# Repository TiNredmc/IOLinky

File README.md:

# IOLinky

IOLinky is an attempt to implement an open-source bare-minimum working IO-Link device.
This project is the part of the undergraduate Automation engineering Co-operative education project while working as R&D internship at Delta Electrnics (Thailand) PCL. From King Mongkut's Institute of Technology Ladkrabang (KMITL). 

**WARNING: THIS SOFTWARE IS NOT MEANT TO BE USED IN COMMERCIAL PRODUCT, I, THIPOK JIAMJARAPAN WILL NOT BE RESPONSIBLE FOR ANY FAILURES/MULFUNCTIONS CAUSED BY THE USE OF THIS SOFTWARE (OR ANY MATERIAL OF THIS PROJECT) IN THE COMMERCIAL PRODUCT, ESPECIALLY SAFETY-RELATED PRODUCT. USER WHO INSISTED TO USE THIS SOFTWARE IN COMMERCIAL PRODUCT WILL HAVE TO TAKE ALL THE RISK ON YOUR OWN. GOOD LUCK, YOU HAVE BE WARNED**

The example application of the IOLinky is the 24 to 5 VDC buck converter, with the feature of input and output monitoring plus Efuse (I2t) implementation.

The original goal of IOLinky is to build the bare-minimum IO-Link compatible device. But the software stack is endded up working quite well. This will soon shifted from a single-use code to the library-code approach. Contribution to project are appreciately welcome!

# Acknowledgement 

This project was made possible by the generous support from these great individuals.
 - **Mr. P. Haribabu**, RD Firmware engineer from **Delta Electronics (Thailand) PCL** for the internship opportunity and project supervision. 
 - **Mr. Steve Liang**, Technical engineer from **STMicroelectronics** for the IO-Link technical support. 
 - **Wurth Electronics (Thailand) Co., Ltd** for providing free component samples to be used in this project.  
 - **Assoc.Prof.Dr. Apinai Rerkratn** from Automation engineering department, school of engineering **KMITL**.

# General Info

- COM modes
    - Peak COM3 response time (L6362A + STM32F042) at **```51.2us```** 
	- Peak COM3 response time (L6362A + GD32E230F8 + New UART API) at **```33.0us```**
    - Cycle time is **```20.00ms```**
    - Supported all COM modes. But may have spec unmet
    - COM3 **SPEC MET✔️**  (IOLinky v1.0 only, for now)
    - COM2 **SPEC MET✔️**
    - COM1 **SPEC MET✔️**

- M-sequence types (Code-customizable)
    - ```M_TYPE_0``` in **Startup** and **Pre-operate** mode
    - ```M_TYPE_2_2``` or ```M_TYPE_2_V``` in **Operate** mode

- Page (Direct parameters)
    - Direct parameter 1 with master command for switching between operation mode
    - Read / Write the Direct parameter 2 is supported

- ISDU 
    - Read / Write system command (unused for now)
    - Basic mandatory info such as Product ID and Vendor ID
    - Process Data Input only (M_TYPE_2_2 and M_TYPE_2_V)

- Process Data
    - 16 Bit PD input with ```M_TYPE_2_2```
    - 8 octet PD input with ```M_TYPE_2_V``` (IOLinky v1.0)
    - PD output is not implemented at this time of writing but possible

# TODO
- Code separation as a standalone library

- M-sequence
    - Check Master's CKT

- ISDU
    - Vendor command for fun
    - Data storage feature
    
- Event
    - Implement event/diagnostic feature

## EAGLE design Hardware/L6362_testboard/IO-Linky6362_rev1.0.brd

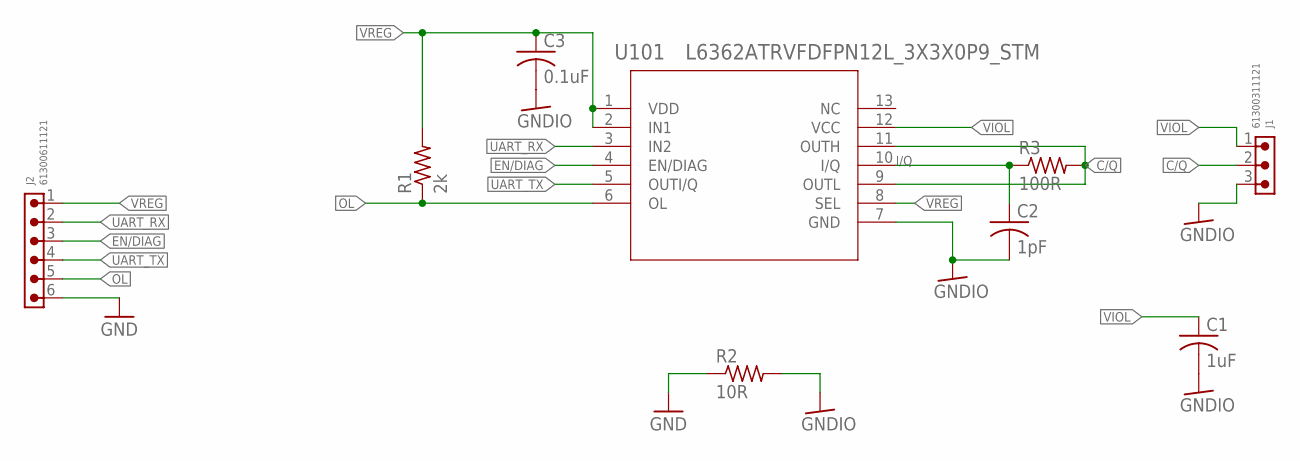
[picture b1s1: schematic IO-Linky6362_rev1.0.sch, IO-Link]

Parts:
C1: 1uF; C0603K
C2: 1pF; C0603K
C3: 0.1uF; C0603K
J1: 61300311121
J2: 61300611121
R1: 2k; R0603
R2: 10R; R0603
R3: 100R; R0603
U101: L6362ATRVFDFPN12L_3X3X0P9_STM; VFDFPN12L_3X3X0P9_STM

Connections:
C/Q: J1.2, R3.2, U101.9 (OUTL), U101.11 (OUTH)
EN/DIAG: J2.3, U101.4 (EN/DIAG)
GND: J2.6, R2.1
GNDIO: C1.2, C2.2, C3.2, J1.3, R2.2, U101.7 (GND)
I/Q: C2.1, R3.1, U101.10 (I/Q)
OL: J2.5, R1.1, U101.6 (OL)
UART_RX: J2.2, U101.3 (IN2)
UART_TX: J2.4, U101.5 (OUTI/Q)
VIOL: C1.1, J1.1, U101.12 (VCC)
VREG: C3.1, J2.1, R1.2, U101.1 (VDD), U101.2 (IN1), U101.8 (SEL)

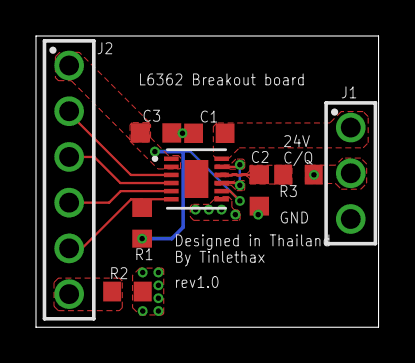
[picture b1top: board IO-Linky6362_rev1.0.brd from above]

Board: 2 copper layers, 19.0 x 16.2 mm, 9 parts (0 on the bottom side), 10 nets.

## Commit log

2024-07-10 Initial
2024-07-10 Updated SPI FSM
2024-07-10 Added dummy hardfault handler.
2024-07-10 Changed Blinking LED to LED2 (Green) and shorten the breathing pattern.
2024-07-10 Change Optimization level back to -Obalance
2024-07-11 Properly check the RXNE flag.
2024-07-18 Place holder for IO-Link System manager.
2024-07-18 Introduced fast FIFO read and write.
2024-07-18 Now using COM2 and changed the polling method.
2024-07-18 Place holder for IO-Link Application layer.
2024-07-18 Added GPIO for monitoring IO-Link activity (for oscilliscope triggering).
2024-07-18 Can reply to Direct parameter 1 and enter PREOPERATE and OPERATE mode. TODO : Reply ISDU in OPREATE MODE.
2024-07-18 Now utilizing Red and Green to show IO-Link connection status. TODO : detect disconnect.
2024-07-18 Moved iol_sm.h to src_iol folder.
2024-07-18 OPERATE mode is now working (NOT FULLY YET). TODO : Complete the ISDU R/W system in DL.
2024-07-18 Updated README.
2024-07-18 Updated Keil project file just to keep it complete.
2024-07-23 Big updates. - Device parameter page 1 data moved to the upper layer (to the Application layer). - Added communication timeout, fall back to STARTUP mode after certain period of time if no comm. - Ad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
2024-07-23 basic ISDU is almost working. TODO : rewrite the PD read.
2024-07-24 Process Data is now working. Added more code comments.
2024-07-24 keep these latest.
2024-07-24 Added checks for L6364 hw fault
    Added a timeout for R/W operations with L6364 cause infinite loops scares af
2024-07-25 Typo fix and minor bugfix
    Fixed some syntax error and a minor bug.
    Calling spi_l6364FastWriteFF with count > 0x0F would have resulted in return 0 (aka 0 bytes remaining to transmit)
2024-07-25 Moved #include "Systick_delay.h" from spi.c to spi.h
    Following mantainer coding standard
2024-07-26 Process Data will only update when necessary to prevent weird bug. IO-Link timeout reset depends on ISDU Flow control Idle command.
2024-07-30 Solved the periodically missing PD data. Added process data write for later use.
2024-07-30 Update PD every 100ms.
2024-07-30 Update to keep track.
2024-07-30 Added schematic and board file for L6362 breakout board(Experiment).
2024-08-01 Added shadow memory for the Process Data.
2024-08-01 Added more ISDU read capabilities.
2024-08-01 Added IODD example file.
2024-08-01 Corrected the ISDU index's endianess.
2024-08-01 Added ISDU write handling (Untested) and currected the memcpy length of ISDU product name.
2024-08-01 added gitignore.
2024-08-01 Moved some part of ISDU data upto the Application layer.
2024-08-01 Changed Process Data display and added unit code.
2024-08-01 Another attempt to fix periodically missing PD, also removed PD write and read funciton (temporary).
2024-08-06 Added code for IOLink-F042. Using L6362 instead of L6364.
2024-08-06 Added L6362A datasheet
2024-08-06 corrected CKS checksum calculation and stripped down the main_fsm.
2024-08-08 Improved response speed, need to test with real L6362A.
2024-08-14 Added missing break in iol_dl_craftISDUWrite().
2024-08-14 removed one line for unknown reason.
2024-08-14 Implemented the Direct parameter 2 and updated Product name.
2024-08-14 EN pin of L6362A will be a forced output instead of Pull-up OD.
2024-08-14 Fixed the missing uart bit and TX switching too early issue.
2024-08-14 Update to keep it in touch.
2024-08-14 Added General Info and TODO.
2024-08-19 function names are now startin with usart. Also preparing for USART DMA TX.
2024-08-19 Added ADC driver.
2024-08-19 PD is not the read value from ADC.
2024-08-19 updated pin out.
2024-08-19 updated function name according to update to usart driver.
2024-08-19 extended timout a bit and also always check mtype before decode the message.
2024-08-19 Update ADC read demo every 20ms.
2024-08-19 Updated IODD bitrate description to COM2.
2024-08-19 Fixed the I-service of ISDU write and also calculated checksum for the reply.
2024-08-27 Added PDF files of first prototype hardware
2024-08-27 Documents for GD32E230F8 that will be used in the first prototype.
2024-08-27 Added code for IOLinky v1.0 (GD32E230 based).
2024-08-28 Added oen highlight to some important details in the datasheet.
2024-08-28 Keep track of the project file.
2024-08-28 TODO : check the time out.
2024-08-28 corrected baud rate on 72MHz APB clock.
2024-08-28 separated IO-Link Data Link layer parts into different files.
2024-08-28 Currently using HXTAL, will revert back to IRC8M soon. As the first prototype doesn't have XTAL.
2024-08-28 Corrected DMA clock bitmask and ADC data pointer before DMA.
2024-08-28 Added ADC. TODO: change message type and wrote the buck converter monitoring system.
2024-08-30 last update for the IOLinkyF042.
2024-08-30 updated schematic of IOLinky V1.0.
2024-08-30 Supported the TYPE2_V and 8 octet PD input data for the upcoming PSU firmware.
2024-08-30 Updated the LED status to be used with TIMER0 PWMM.
2024-08-30 - Changed OPERATE M-sequence to TYPE2_V with 8 PD in octets - Lean down the iol_dl_craftISDURead() fuction.
2024-08-30 PD cycle is now 20ms and using TYP2_V message with 8 PD in data.
2024-08-30 Use the slowest sample rate. ADC startup delay is now wokring with -O balanced.
2024-08-30 Added PSU application.
2024-08-30 Keep track of the project configuration.
2024-08-30 Update datasheet with highlighted important pins.
2024-08-30 changed min pd cycle time to 20,000us (20ms).
2024-08-30 Swapped the calculation of Vin and Vout.
2024-08-30 Switch back to IRC8M instead of HXTAL as the actual board doesn't use xtal. Will add xtal later if the board need to respin.
2024-08-30 Vout undervoltage will only notify when buck converter is commanded to be on.
2024-09-02 Updated text information.
2024-09-02 Changed ADC buffer pointer type to 16bit.
2024-09-02 Added peak current along side the Nominal High and Short circuit.
2024-09-02 Updated monitoring logic.
2024-09-02 Changed ADC buffer pointer type and few changes to the FSM.
2024-09-02 LED PWM is now working.
2024-09-02 LED status is now breathing.
2024-09-09 Corrected the PLL multiplier for IRC8M to get 72MHz sysclock.
2024-09-09 Removed the unused pin and changed speed of LED task.
2024-09-09 reset index at init of L6362A.
2024-09-09 No need the included system clock config.
2024-09-09 Board view PDF update and added Fusion 360 archive file.
2024-09-09 Added fault indicator LED mode.
2024-09-09 Input undervoltage detection now operate with hysteresis.
2024-09-09 update main.c description.
2024-09-09 Only allows power on when Vin is ok.
2024-09-10 Tuned timeout to be faster.
2024-09-10 Efuse algorithm small changes. Efuse accumulator will be using int32_t.
2024-09-10 Updated Input voltage ADC conversion factor to 0.00747.
2024-09-10 Now getting the actual 72MHz running.
2024-09-10 Make sure that PD in reading with ISUD is sent out with Big endianess.
2024-09-10 temporary changes the resistor divider calculation value. Need more investigation.
2024-09-10 Fine tuned the USART baud rate.
2024-09-10 Make IO-Link comm timeout delay longer to almost 2 seconds.
2024-09-10 Corrected the F_CPU value used for Systick. As well as LED task period.
2024-09-10 Added 3 seconds hiccup mode and handled the Vout fault properly.
2024-09-11 formatting it nicely.
2024-09-11 IO-Link activity monitoring (debg) pins moved to PA0.
2024-09-11 - API changes to UART driver - to allow the response time in COM3 mode from >43us MAX to just 33.0us MAX.
2024-09-13 Added debug menu for Specialist menu set.
2024-09-13 PSU fsm state and Efuse counter can be read from ISDU.
2024-09-13 Updated Logic of PSU, Efuse is now working properly. TODO : - Efuse setting via IO-Link ISDU - Calibration value and compenstation.
2024-09-20 Updated IODD to accomodate for the parameter and calibrations through ISDU.
2024-09-20 Huge update. [PSU and IO-Link side] - PSU power on/off, Efuse Amp Trip, Period Hold and ADC calibration value are now accessible via ISDU (some RW, some RO, some WO). - Added app_nvm for retrieve and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
2024-09-20 Just keep in touch with these project file.
2024-09-20 New linker script to reserve the upper portion of flash memory for calibration and efuse data.
2024-09-23 Keep update in touch.
2024-09-23 IO-Link stack is now almost totally separated from BSP.
2024-09-23 Output current good indicator only works in PSU on mode.
2024-09-23 removed debugging GPIO.
2024-09-23 unified M-Sequence handler.
2024-09-23 Initialize physical layer and setup the callback pointer before start the stack.
2024-09-27 Added Diagnosis Communication channel handling (Events code).
2024-09-27 Moved LED from the iol_pl to user app.
2024-09-27 Change writing style.
2024-10-09 Added IO-Link event report api call for app layer.
2024-10-09 PSU app can report IO-Link event by using iol_al api call.
2024-10-09 Added the mechanical design for the IOLinky V1.0.
2024-10-16 Fixed the Short circuit flag.
2024-12-09 Updated README to include the Acknowledgement.

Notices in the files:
parts and their libraries:
Wurth_Connectors_WR-PHD: Copyright: Würth Elektronik
COPYRIGHT: Copyright (C) 2024 Ultra Librarian. All rights reserved.
